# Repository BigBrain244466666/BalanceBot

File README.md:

# The Balancer

**Description**: This is a robot that can autonomously balance on two wheels while being controlled with regular movements (forward, backward, left, right) via Bluetooth on a computer.

**Why I did this project**: I found this project online when searching for good robotics challenges. It sounded fun because I had just seen things like hoverboards (those two-wheel boards that you can ride on) and thought it would be cool if I could make a miniature version of them. Of course, the design isn't the same, but it's the same concept.

**Description of Files**
My files may be a bit confusing, so I'm going to go through them.

- CAD: This one's pretty straightforward; it's the entire build in a .step file.
- PCB: Here is the main stuff. There are two schematics, one for the breakout boards and one to show the real wiring. The breakout board one exists as I am using non-SMD parts, and all the footprints I could find online are using SMD, so I used pads on the real PCB to connect them to the breakout boards. When referencing the wiring, please use the **Balance Bot - Real.kicad_sch** file. Also, the kicad_pro file only includes the PCB due for this reason, when looking at them, please open the schematics separately.
- Production: Here are all my production files, including the top, middle, bottom, and motor holder step files. Also included is the PCB gerber file.
- Wiring: A Fritzing file is attached here to see the wiring of the motors and battery packs, as those wires are not included in the CAD file.
- Firmware: Firmware was not included due to it being too dependent on the physical bot (measurements and calibrating the gyroscope).

**BOM**

Item # |	Part Name |	Quantity |	Description |	Source |	Cost (CAD)
--- | --- | --- | --- | --- | ---
1 |	Raspberry Pi Pico W |	1 |	Microcontroller |	AliExpress | 15.37
2 |	DRV8833 |	1 |	Motor Driver |	AdaFruit | 5.95
3 |	Mpu6040 |	1 |	Gyroscope |	AdaFruit | 12.95
4 |	Motor and Wheels |	1 |	Kit |	Temu | 10
5 |	PCB |	5 |	Pack |	PCBWay | 5
6 |	Chassis |	1 |	Bottom, 191 g |	Waterloo Public Library |	6
7 |	Chassis |	1 |	Middle, 100 g |	Waterloo Public Library |	4
8 |	Chassis |	1 |	Top, 40 g |	Waterloo Public Library |	2
9 |	Chassis |	8 |	Motor Holder, 0.74 g |	Waterloo Public Library |	1
10 |	Screws, M3 |	1 |	25 Pc |	AliExpress |	4.39
11 | Bolts, M3 |	1 |	25 Pc | AliExpress |	2.71
12 |	Googly Eyes |	1 |	10 Pc |	AliExpress |	3.47
13 |	Batteries |	2 |	4 and 2 AA holder |	AliExpress | 5
14 | Shipping | N/A |	N/A |	N/A |	20-40

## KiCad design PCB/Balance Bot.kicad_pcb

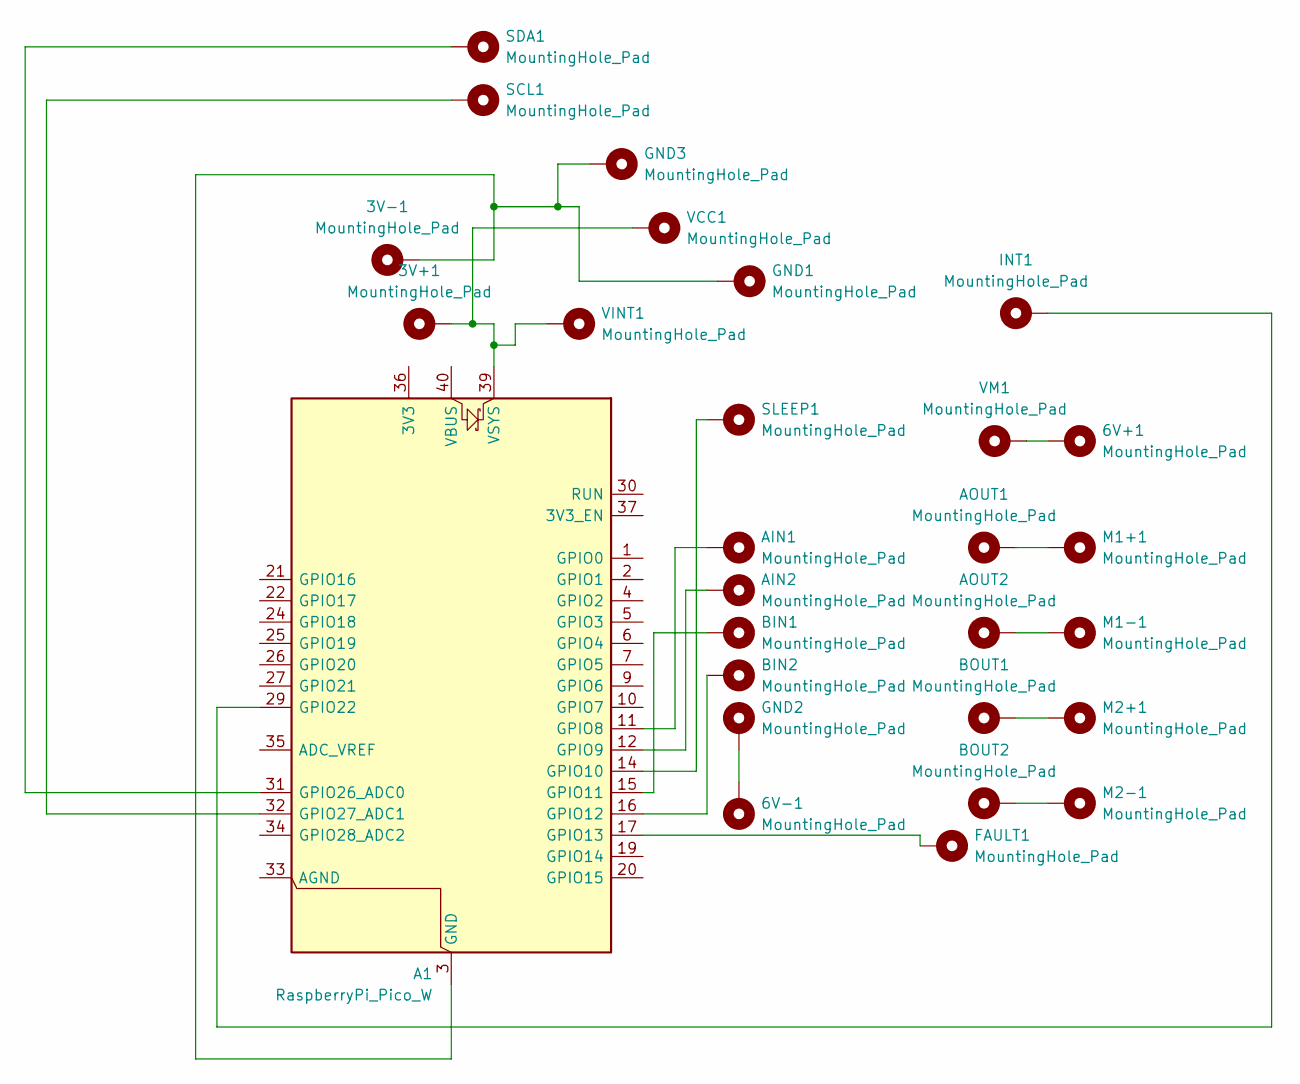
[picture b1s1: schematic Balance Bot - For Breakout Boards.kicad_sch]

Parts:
3V+1, 3V-1, 6V+1, 6V-1: MountingHole_Pad; SolderWirePad_1x01_SMD_1x2mm
A1: RaspberryPi_Pico_W; RaspberryPi_Pico_W_SMD_HandSolder
AIN1, AIN2: MountingHole_Pad; SolderWirePad_1x01_SMD_1x2mm
AOUT1, AOUT2: MountingHole_Pad; SolderWirePad_1x01_SMD_1x2mm
BIN1, BIN2: MountingHole_Pad; SolderWirePad_1x01_SMD_1x2mm
BOUT1, BOUT2: MountingHole_Pad; SolderWirePad_1x01_SMD_1x2mm
FAULT1: MountingHole_Pad; SolderWirePad_1x01_SMD_1x2mm
GND1, GND2, GND3: MountingHole_Pad; SolderWirePad_1x01_SMD_1x2mm
INT1: MountingHole_Pad; SolderWirePad_1x01_SMD_1x2mm
M1+1, M1-1, M2+1, M2-1: MountingHole_Pad; SolderWirePad_1x01_SMD_1x2mm
SCL1: MountingHole_Pad; SolderWirePad_1x01_SMD_1x2mm
SDA1: MountingHole_Pad; SolderWirePad_1x01_SMD_1x2mm
SLEEP1: MountingHole_Pad; SolderWirePad_1x01_SMD_1x2mm
VCC1: MountingHole_Pad; SolderWirePad_1x01_SMD_1x2mm
VINT1: MountingHole_Pad; SolderWirePad_1x01_SMD_1x2mm
VM1: MountingHole_Pad; SolderWirePad_1x01_SMD_1x2mm

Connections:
unnamed: 3V-1.1, A1.3 (GND), A1.8 (GND), A1.13 (GND), A1.18 (GND), A1.23 (GND), A1.28 (GND), A1.38 (GND), GND1.1, GND3.1
unnamed: 6V+1.1, VM1.1
unnamed: 6V-1.1, GND2.1
unnamed: A1.11 (GPIO8), AIN1.1
unnamed: A1.12 (GPIO9), AIN2.1
unnamed: A1.14 (GPIO10), SLEEP1.1
unnamed: A1.15 (GPIO11), BIN1.1
unnamed: A1.16 (GPIO12), BIN2.1
unnamed: A1.17 (GPIO13), FAULT1.1
unnamed: A1.29 (GPIO22), INT1.1
unnamed: A1.31 (GPIO26_ADC0), SDA1.1
unnamed: A1.32 (GPIO27_ADC1), SCL1.1
unnamed: 3V+1.1, A1.39 (VSYS), VCC1.1, VINT1.1
unnamed: AOUT1.1, M1+1.1
unnamed: AOUT2.1, M1-1.1
unnamed: BOUT1.1, M2+1.1
unnamed: BOUT2.1, M2-1.1

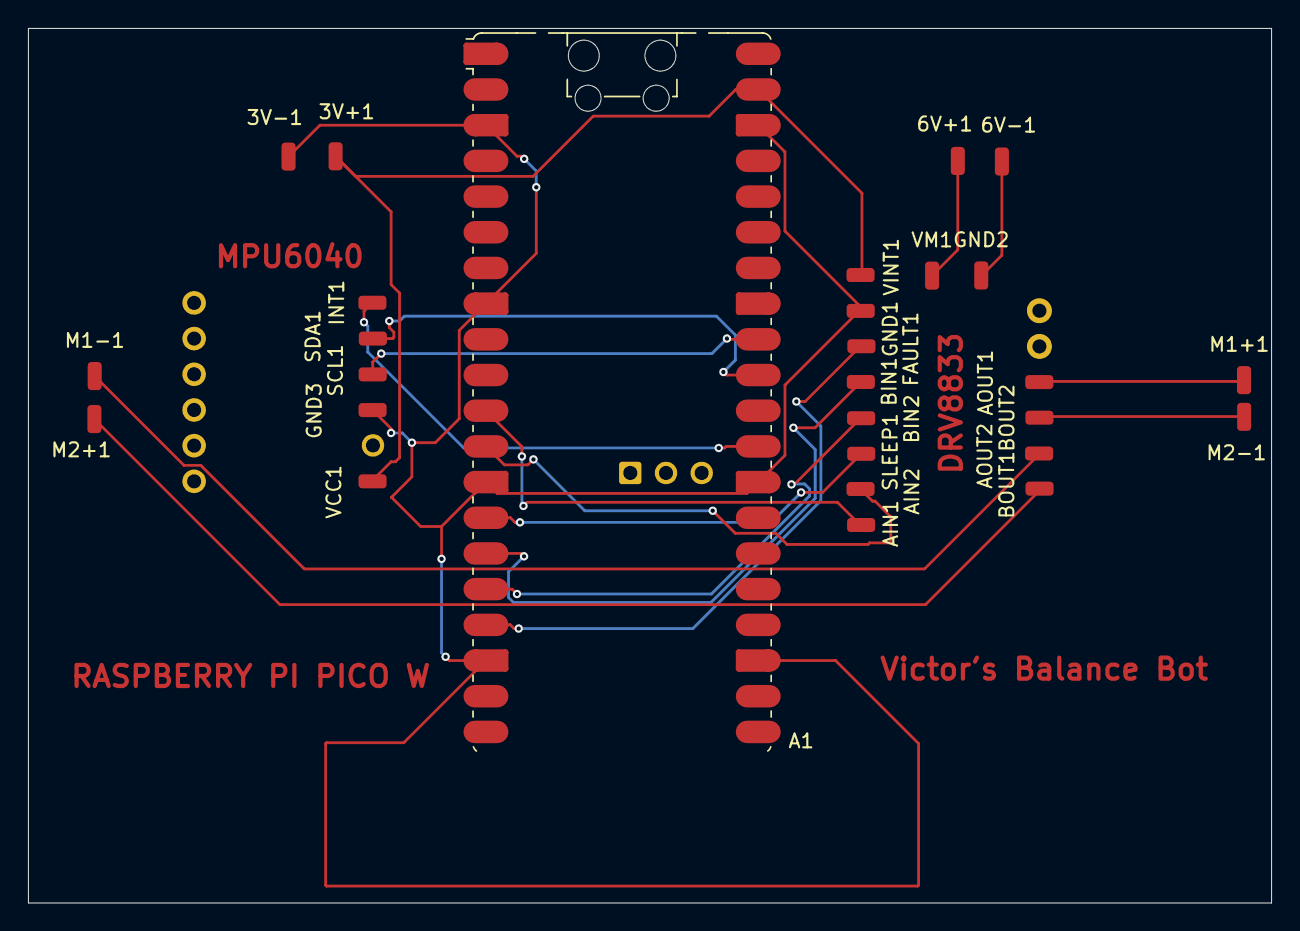
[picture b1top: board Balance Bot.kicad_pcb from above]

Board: 2 copper layers, 88.5 x 62.2 mm, 30 parts (0 on the bottom side), 17 nets.

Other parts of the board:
JP2: 1X06_ROUND
JP4: 1X02_ROUND

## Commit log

2025-06-07 Add new large file
2025-06-08 Add images
2025-06-09 Rename main.py to Firmware/main.py
